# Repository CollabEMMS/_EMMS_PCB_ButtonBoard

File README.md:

# _EMMS_PCB_ButtonBoard
Button Board PCB files
<p>Confirmed Latest Version as 2/6/2020

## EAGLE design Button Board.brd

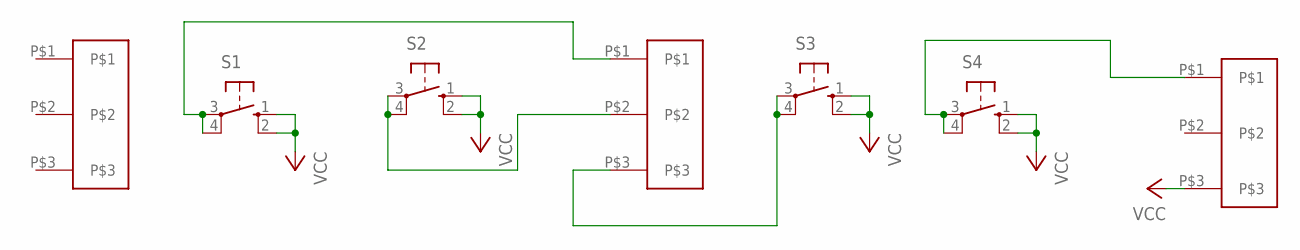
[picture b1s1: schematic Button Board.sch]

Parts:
S1, S2, S3, S4: 40-XX; B3F-40XX
U$1, U$2, U$3: 3_PIN_FEMALE_HEADER

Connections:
unnamed: S1.3, S1.4 (P1), U$2.P$1
unnamed: S2.3, S2.4 (P1), U$2.P$2
unnamed: S3.3, S3.4 (P1), U$2.P$3
unnamed: S4.3, S4.4 (P1), U$3.P$1
VCC: S1.1 (S), S1.2 (S1), S2.1 (S), S2.2 (S1), S3.1 (S), S3.2 (S1), S4.1 (S), S4.2 (S1), U$3.P$3

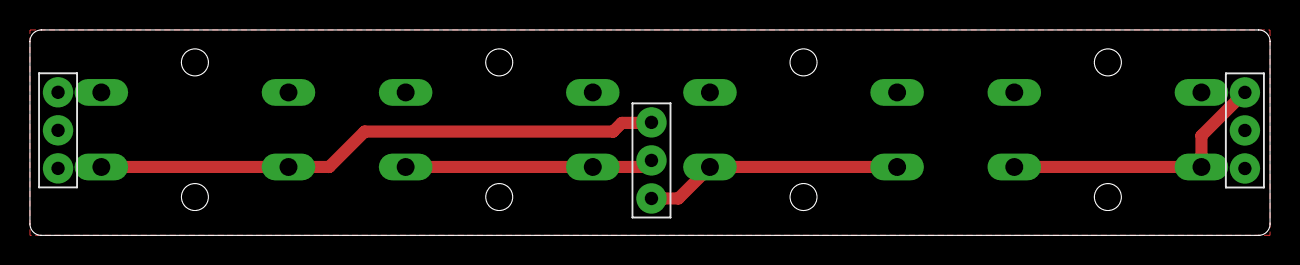
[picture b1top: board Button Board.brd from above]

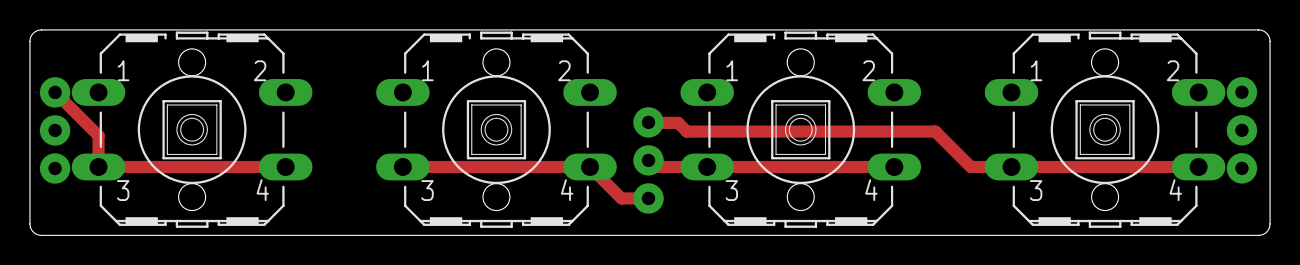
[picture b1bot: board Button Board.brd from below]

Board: 2 copper layers, 82.8 x 13.7 mm, 7 parts (4 on the bottom side), 5 nets.

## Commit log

2020-02-06 Button Board PCB files added
    This is the most current design as of today, February 6th 2020
2020-02-06 Uploading Gerbers
    Copied from where they were in the UIBoard
